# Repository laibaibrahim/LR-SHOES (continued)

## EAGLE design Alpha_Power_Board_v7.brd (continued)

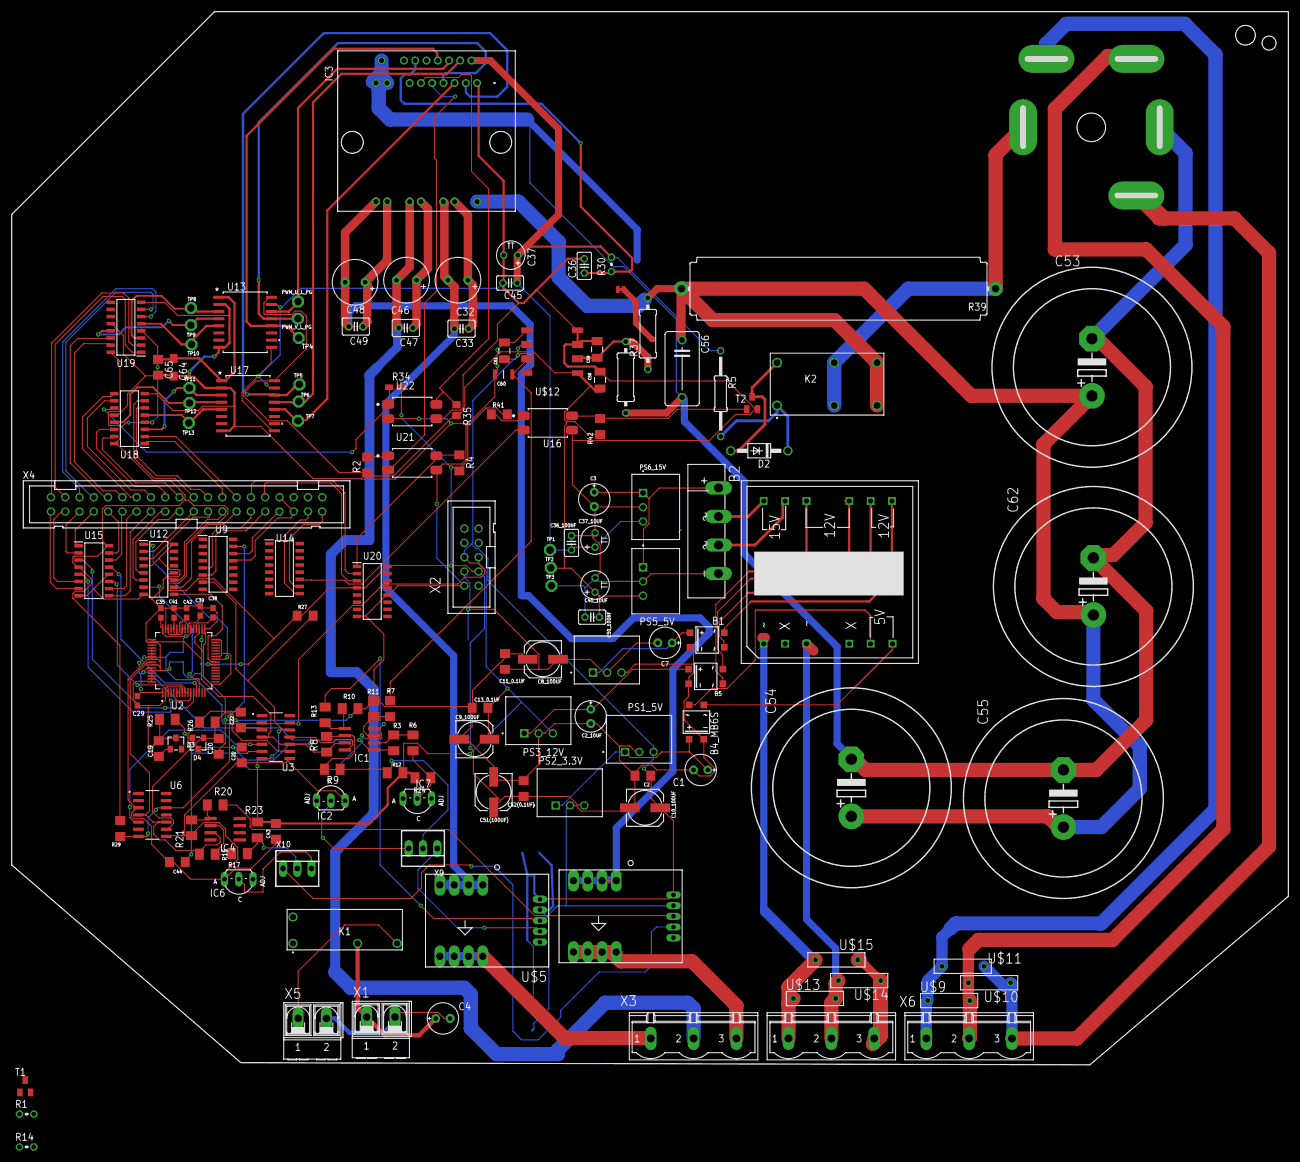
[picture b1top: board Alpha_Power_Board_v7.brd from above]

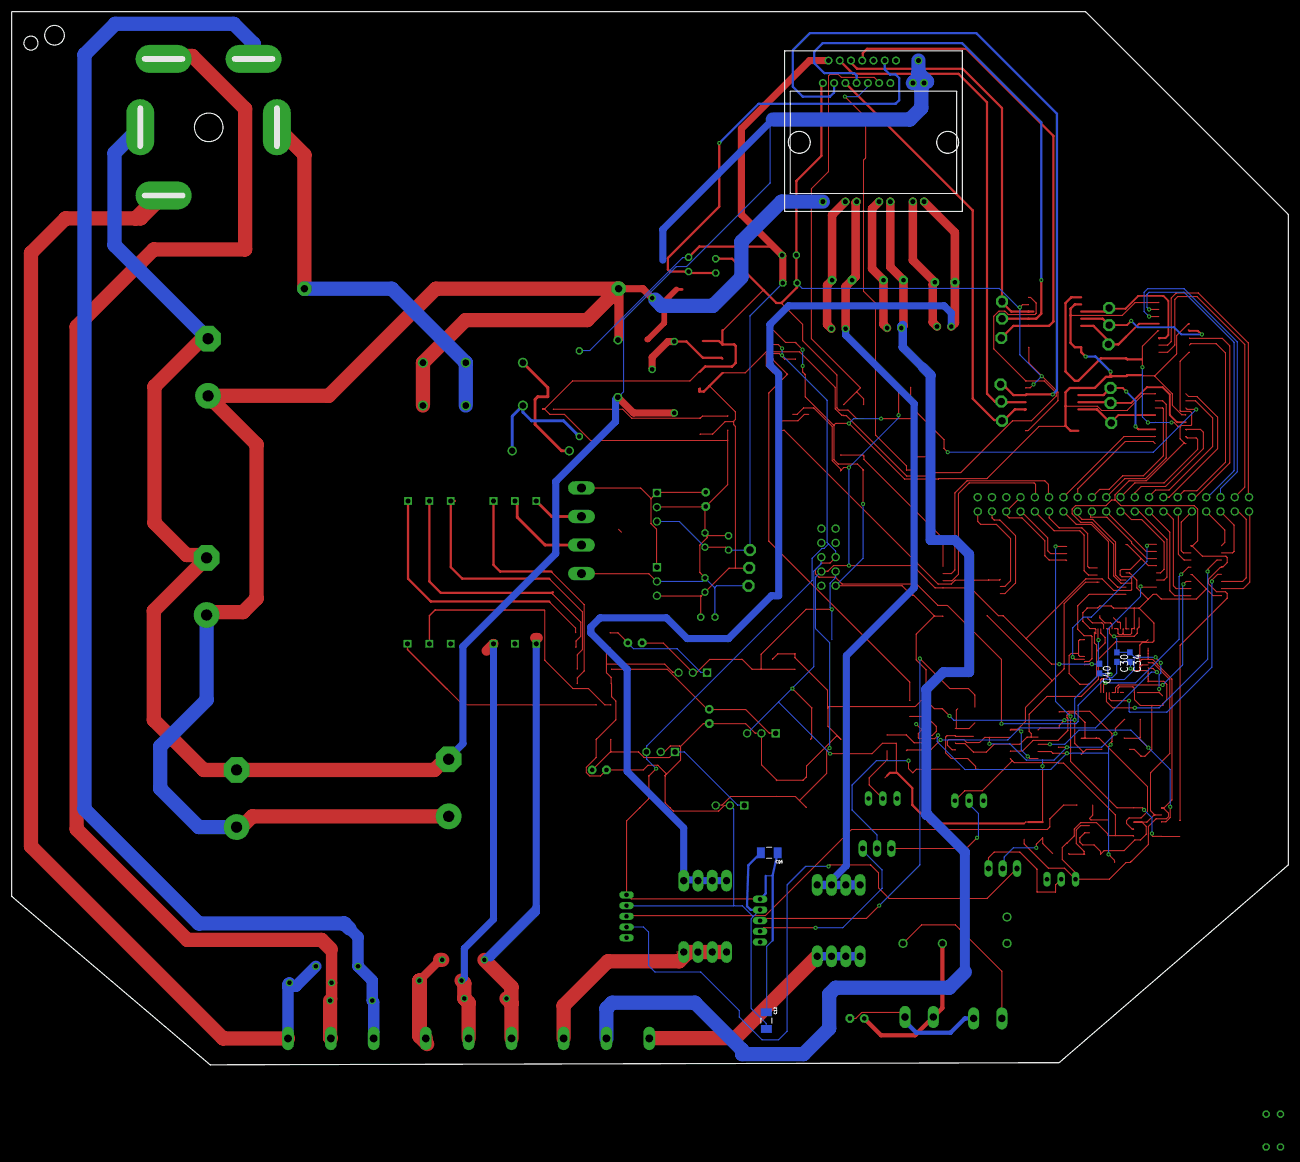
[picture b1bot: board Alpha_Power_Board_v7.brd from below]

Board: 4 copper layers, 227.1 x 187.3 mm, 160 parts (5 on the bottom side), 136 nets.

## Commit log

2024-01-19 LR SHOES
2024-01-20 First comit
